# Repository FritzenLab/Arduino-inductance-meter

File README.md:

# Arduino-inductance-meter
 An inductance meter with 555 and Arduino

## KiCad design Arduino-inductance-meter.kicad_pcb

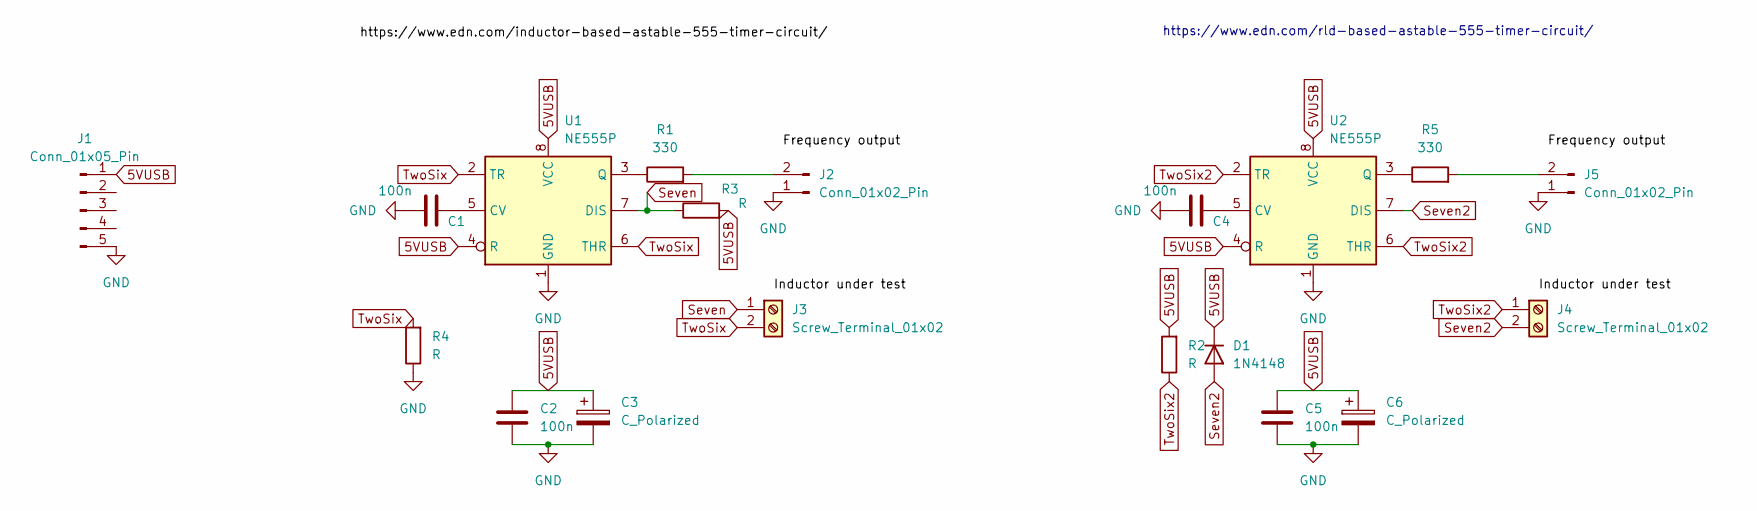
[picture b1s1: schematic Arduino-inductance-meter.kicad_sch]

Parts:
C1, C2, C4, C5: 100n; C_0805_2012Metric
C3, C6: C_Polarized; CP_Radial_D5.0mm_P2.50mm
D1: 1N4148; D_DO-35_SOD27_P7.62mm_Horizontal
J1: Conn_01x05_Pin; PinHeader_1x05_P2.54mm_Vertical
J2, J5: Conn_01x02_Pin; PinHeader_1x02_P2.54mm_Vertical
J3, J4: Screw_Terminal_01x02; TerminalBlock_Phoenix_MKDS-3-2-5.08_1x02_P5.08mm_Horizontal
R1, R5: 330; R_0805_2012Metric
R2, R3, R4: R; R_Axial_DIN0411_L9.9mm_D3.6mm_P12.70mm_Horizontal
U1, U2: NE555P; DIP-8_W7.62mm

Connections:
5VUSB: C2.2, C3.1, C5.2, C6.1, D1.1 (K), J1.1, R2.2, R3.2, U1.4 (R), U1.8 (VCC), U2.4 (R), U2.8 (VCC)
GND: C1.1, C2.1, C3.2, C4.1, C5.1, C6.2, J1.5, J2.1, J5.1, R4.1, U1.1 (GND), U2.1 (GND)
unnamed: J2.2, R1.2
unnamed: J5.2, R5.2
unnamed: C1.2, U1.5 (CV)
unnamed: R1.1, U1.3 (Q)
unnamed: C4.2, U2.5 (CV)
unnamed: R5.1, U2.3 (Q)
Seven: J3.1, R3.1, U1.7 (DIS)
Seven2: D1.2 (A), J4.2, U2.7 (DIS)
TwoSix: J3.2, R4.2, U1.2 (TR), U1.6 (THR)
TwoSix2: J4.1, R2.1, U2.2 (TR), U2.6 (THR)

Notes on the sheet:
https://www.edn.com/rld-based-astable-555-timer-circuit/

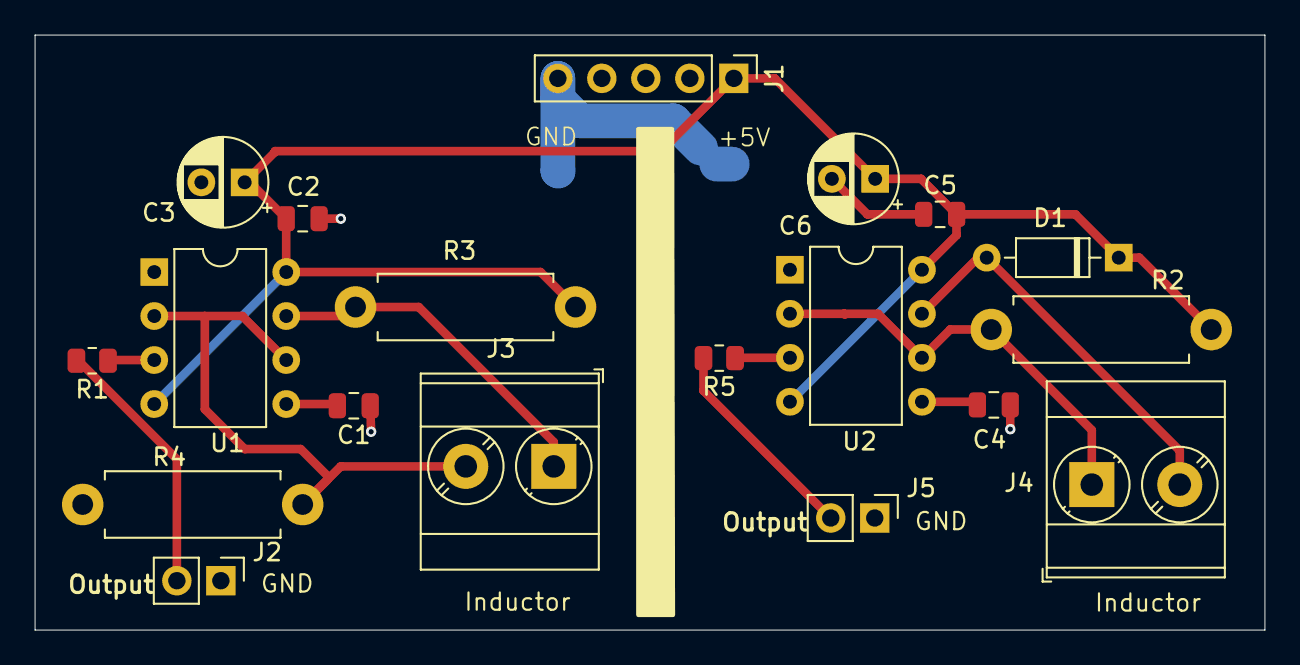
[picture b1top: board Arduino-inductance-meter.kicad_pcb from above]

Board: 2 copper layers, 71.0 x 34.3 mm, 19 parts (0 on the bottom side), 12 nets.

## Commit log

2024-10-16 Created schematics
2024-10-16 finished layout, not verified
2024-10-17 backups
2024-10-18 Gerber generated
